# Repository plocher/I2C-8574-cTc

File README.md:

# I2C-8574-cTc
## License: CERN Open Hardware Licence v1.2

I2C PCF8574-based IO Expander cTc Wiring Harness

Simple PCBs to help with taming the wiring ratsnest found behind a CTC machine’s panels.

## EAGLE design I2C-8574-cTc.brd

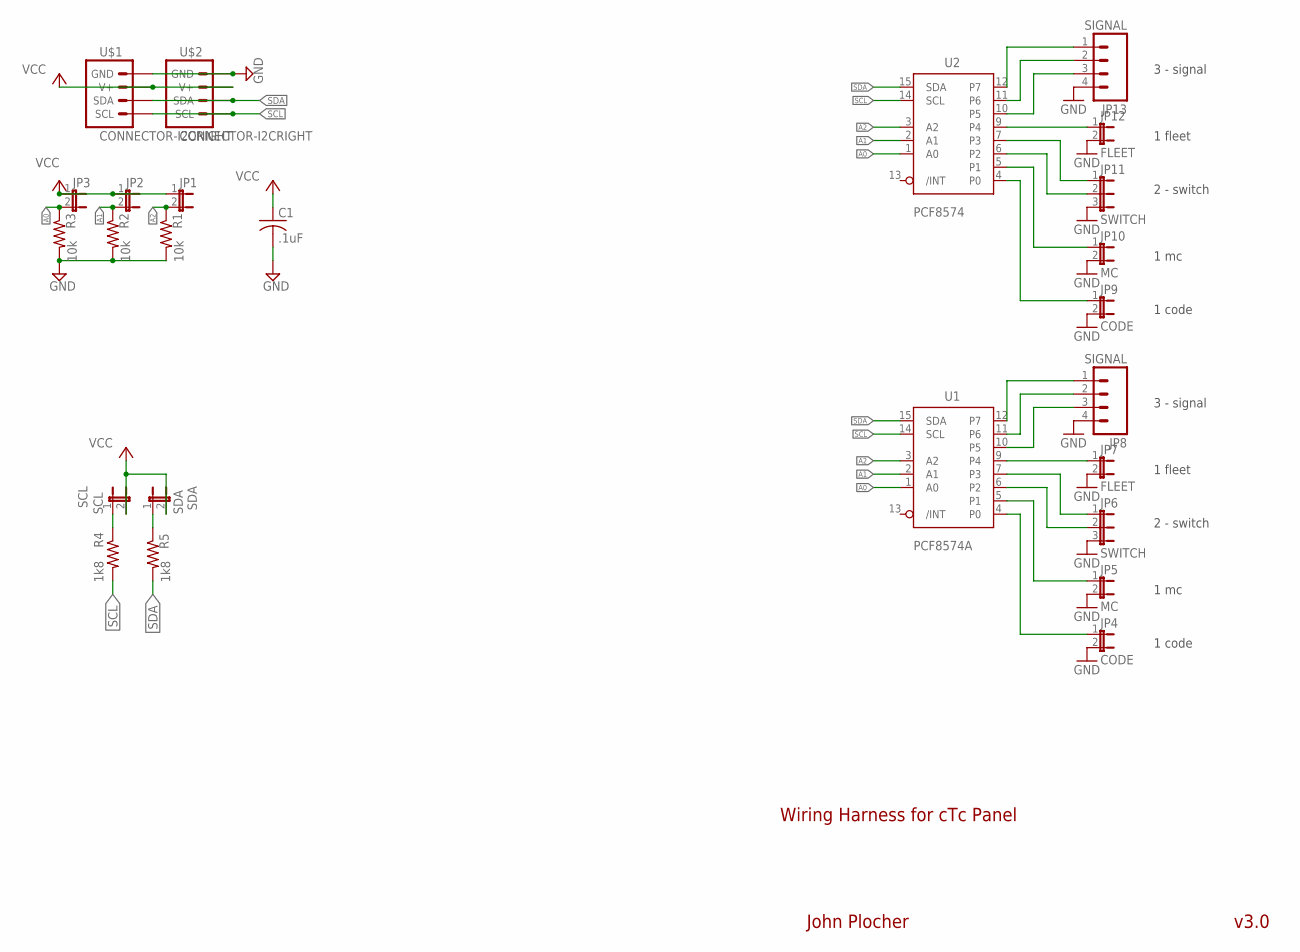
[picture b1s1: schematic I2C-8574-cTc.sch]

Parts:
C1: .1uF; 0805-CAP
JP1, JP2, JP3: JUMPER-2SMD-NO; SJ_2S-NO
JP4, JP9: CODE; 1X02_LOCK
JP5, JP10: MC; 1X02_LOCK
JP6, JP11: SWITCH; 1X03
JP7, JP12: FLEET; 1X02_LOCK
JP8, JP13: SIGNAL; 1X04_LOCK
R1, R2, R3: 10k; 0805-RES
R4, R5: 1k8; 0805-RES
SCL: SCL; 1X02_LOCK
SDA: SDA; 1X02_LOCK
U1: PCF8574A; SO-16DW
U2: PCF8574; SO-16DW
U$1, U$2: CONNECTOR-I2CRIGHT; I2C-R

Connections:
A0: JP3.2, R3.1, U1.1 (A0), U2.1 (A0)
A1: JP2.2, R2.1, U1.2 (A1), U2.2 (A1)
A2: JP1.2, R1.1, U1.3 (A2), U2.3 (A2)
CODE0: JP4.1, U1.4 (P0)
CODE1: JP9.1, U2.4 (P0)
FLEET0: JP7.1, U1.9 (P4)
FLEET1: JP12.1, U2.9 (P4)
GND: C1.2, JP4.2, JP5.2, JP6.3, JP7.2, JP8.4, JP9.2, JP10.2, JP11.3, JP12.2, JP13.4, R1.2, R2.2, R3.2, U1.8 (GND), U2.8 (GND), U$1.GND, U$1.GND@1 (GND), U$2.GND, U$2.GND@1 (GND)
LEFT0: JP8.3, U1.10 (P5)
LEFT1: JP13.3, U2.10 (P5)
MC0: JP5.1, U1.5 (P1)
MC1: JP10.1, U2.5 (P1)
N0: JP6.2, U1.6 (P2)
N1: JP11.2, U2.6 (P2)
unnamed: R5.1, SDA.1
unnamed: R4.1, SCL.1
R0: JP6.1, U1.7 (P3)
R1: JP11.1, U2.7 (P3)
RIGHT0: JP8.1, U1.12 (P7)
RIGHT1: JP13.1, U2.12 (P7)
SCL: R4.2, U1.14 (SCL), U2.14 (SCL), U$1.SCL, U$1.SCL@1 (SCL), U$2.SCL, U$2.SCL@1 (SCL)
SDA: R5.2, U1.15 (SDA), U2.15 (SDA), U$1.SDA, U$1.SDA@1 (SDA), U$2.SDA, U$2.SDA@1 (SDA)
STOP0: JP8.2, U1.11 (P6)
STOP1: JP13.2, U2.11 (P6)
VCC: C1.1, JP1.1, JP2.1, JP3.1, SCL.2, SDA.2, U1.16 (VCC), U2.16 (VCC), U$1.V+, U$1.V+@1 (V+), U$2.V+, U$2.V+@1 (V+)

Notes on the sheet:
2 - switch
3 - signal
1 code
1 mc
1 fleet
Wiring Harness for cTc Panel
John Plocher
v3.0

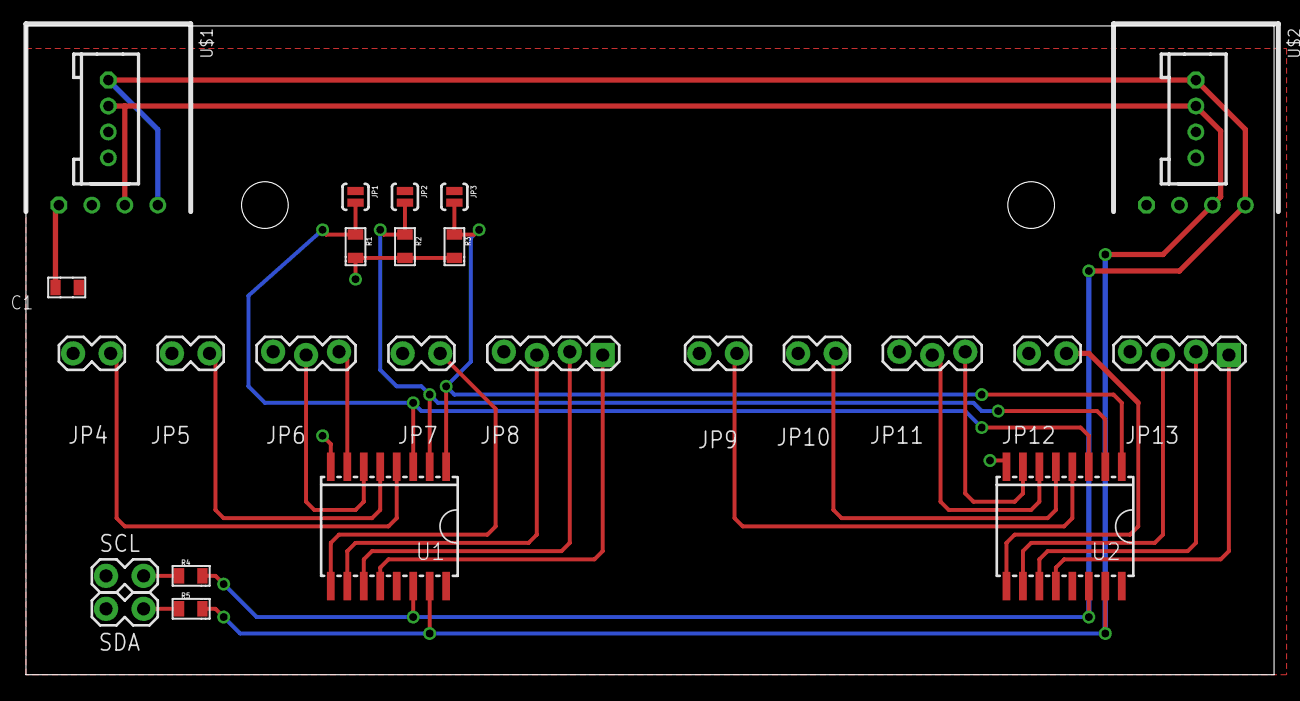
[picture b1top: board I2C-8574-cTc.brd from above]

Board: 2 copper layers, 96.2 x 50.0 mm, 25 parts (0 on the bottom side), 25 nets.

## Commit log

2020-05-04 updated tags
